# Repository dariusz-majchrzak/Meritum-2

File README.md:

# Meritum-2: Polish 8-bit Home Computer
This project was initiated with the goal of converting the old, incomplete, and often difficult-to-read documentation of the Meritum II computer into a digital CAD design. It provides a solid foundation for further research, reconstruction efforts, and experimentation by anyone interested in the technical aspects of the early days of Polish computing and the development of domestically designed 8-bit computers.<br>

All files required to build a hardware reproduction of the **Meritum 1 (Model 2) (commonly known as Meritum2)** ( https://pl.wikipedia.org/wiki/Meritum_(komputer) ) are provided in this repository. The project closely follows the design of one of the earliest microcomputers to be mass-produced in Poland.<br>

**Meritum 1 (Model 2) = Meritum2** <br>
Basic Technical Specifications:
* RAM: 48 KB (RAMD)
* ROM: 14 KB (BASIC)
* Video Memory: 1 KB (RAMS)
* Display Modes: Text — 16×64 or 16×32
* Peripherals: serial interface (i8251), parallel interface (i8255), tape interface, fdd interface (i8255)
* Colors: Monochrome
<br>
As of November 11, 2026, there is one successful build based on this PCB revision and three successful builds based on a previous PCB revision.<br>

As additional fixes were identified during testing, the repository includes an updated PCB revision (Rev. 1.2), whereas the PCB shown in the photo is Rev. 1.1. <br>
<br>

Top view of the mainboard:<br>

Side view of the computer with connectors:<br>

Example startup screen:<br>

Important notes:<br>
* Please note that this is a complex hardware project that requires solid technical expertise from anyone who decides to build it.<br>
* While significant care has been taken during the design and verification process, the project may still need additional fixes, especially if the original design included fixes implemented directly at the PCB level that were not reflected in the published schematics.

## PCBs
The clone consists of two separate PCBs:
* [Meritum2_PGW](Meritum2_PGW) (Meritum Płyta Główna) - is the main board.
* [Meritum2_KLT](Meritum2_KLT) (Meritum Klawiatura) - is a replacement keyboard that uses standard Cherry MX switches.

## ROMs
Since the licensing status of the ROMs used in the Meritum 2 computer is not clear to me, I have not included them in this repository.<br> 
Below, however, I provide links to a websites where they can be found, along with many other valuable resources:
* https://web.archive.org/web/20201023154655/https://sites.google.com/site/krzkomar/meritum-1
* https://www.planetemu.net/rom/mame-roms-merged/meritum1<br>
  
Many useful materials can also be found at: https://www.speccy.pl/news.php .

## Assembling
Although the mainboard includes several configuration jumpers, it does not require any additional settings that need to be adjusted before powering it on. The default configuration is sufficient.<br>

To connect mainboard with keyboard I have used:
-  single and double Row, 2.54mm straight, Gold PCB Female Sockets Connector
-  single and double Row, 2.54mm straight, Gold PCB Male Pin Header connector (h=29.5mm)
  
More to follow.

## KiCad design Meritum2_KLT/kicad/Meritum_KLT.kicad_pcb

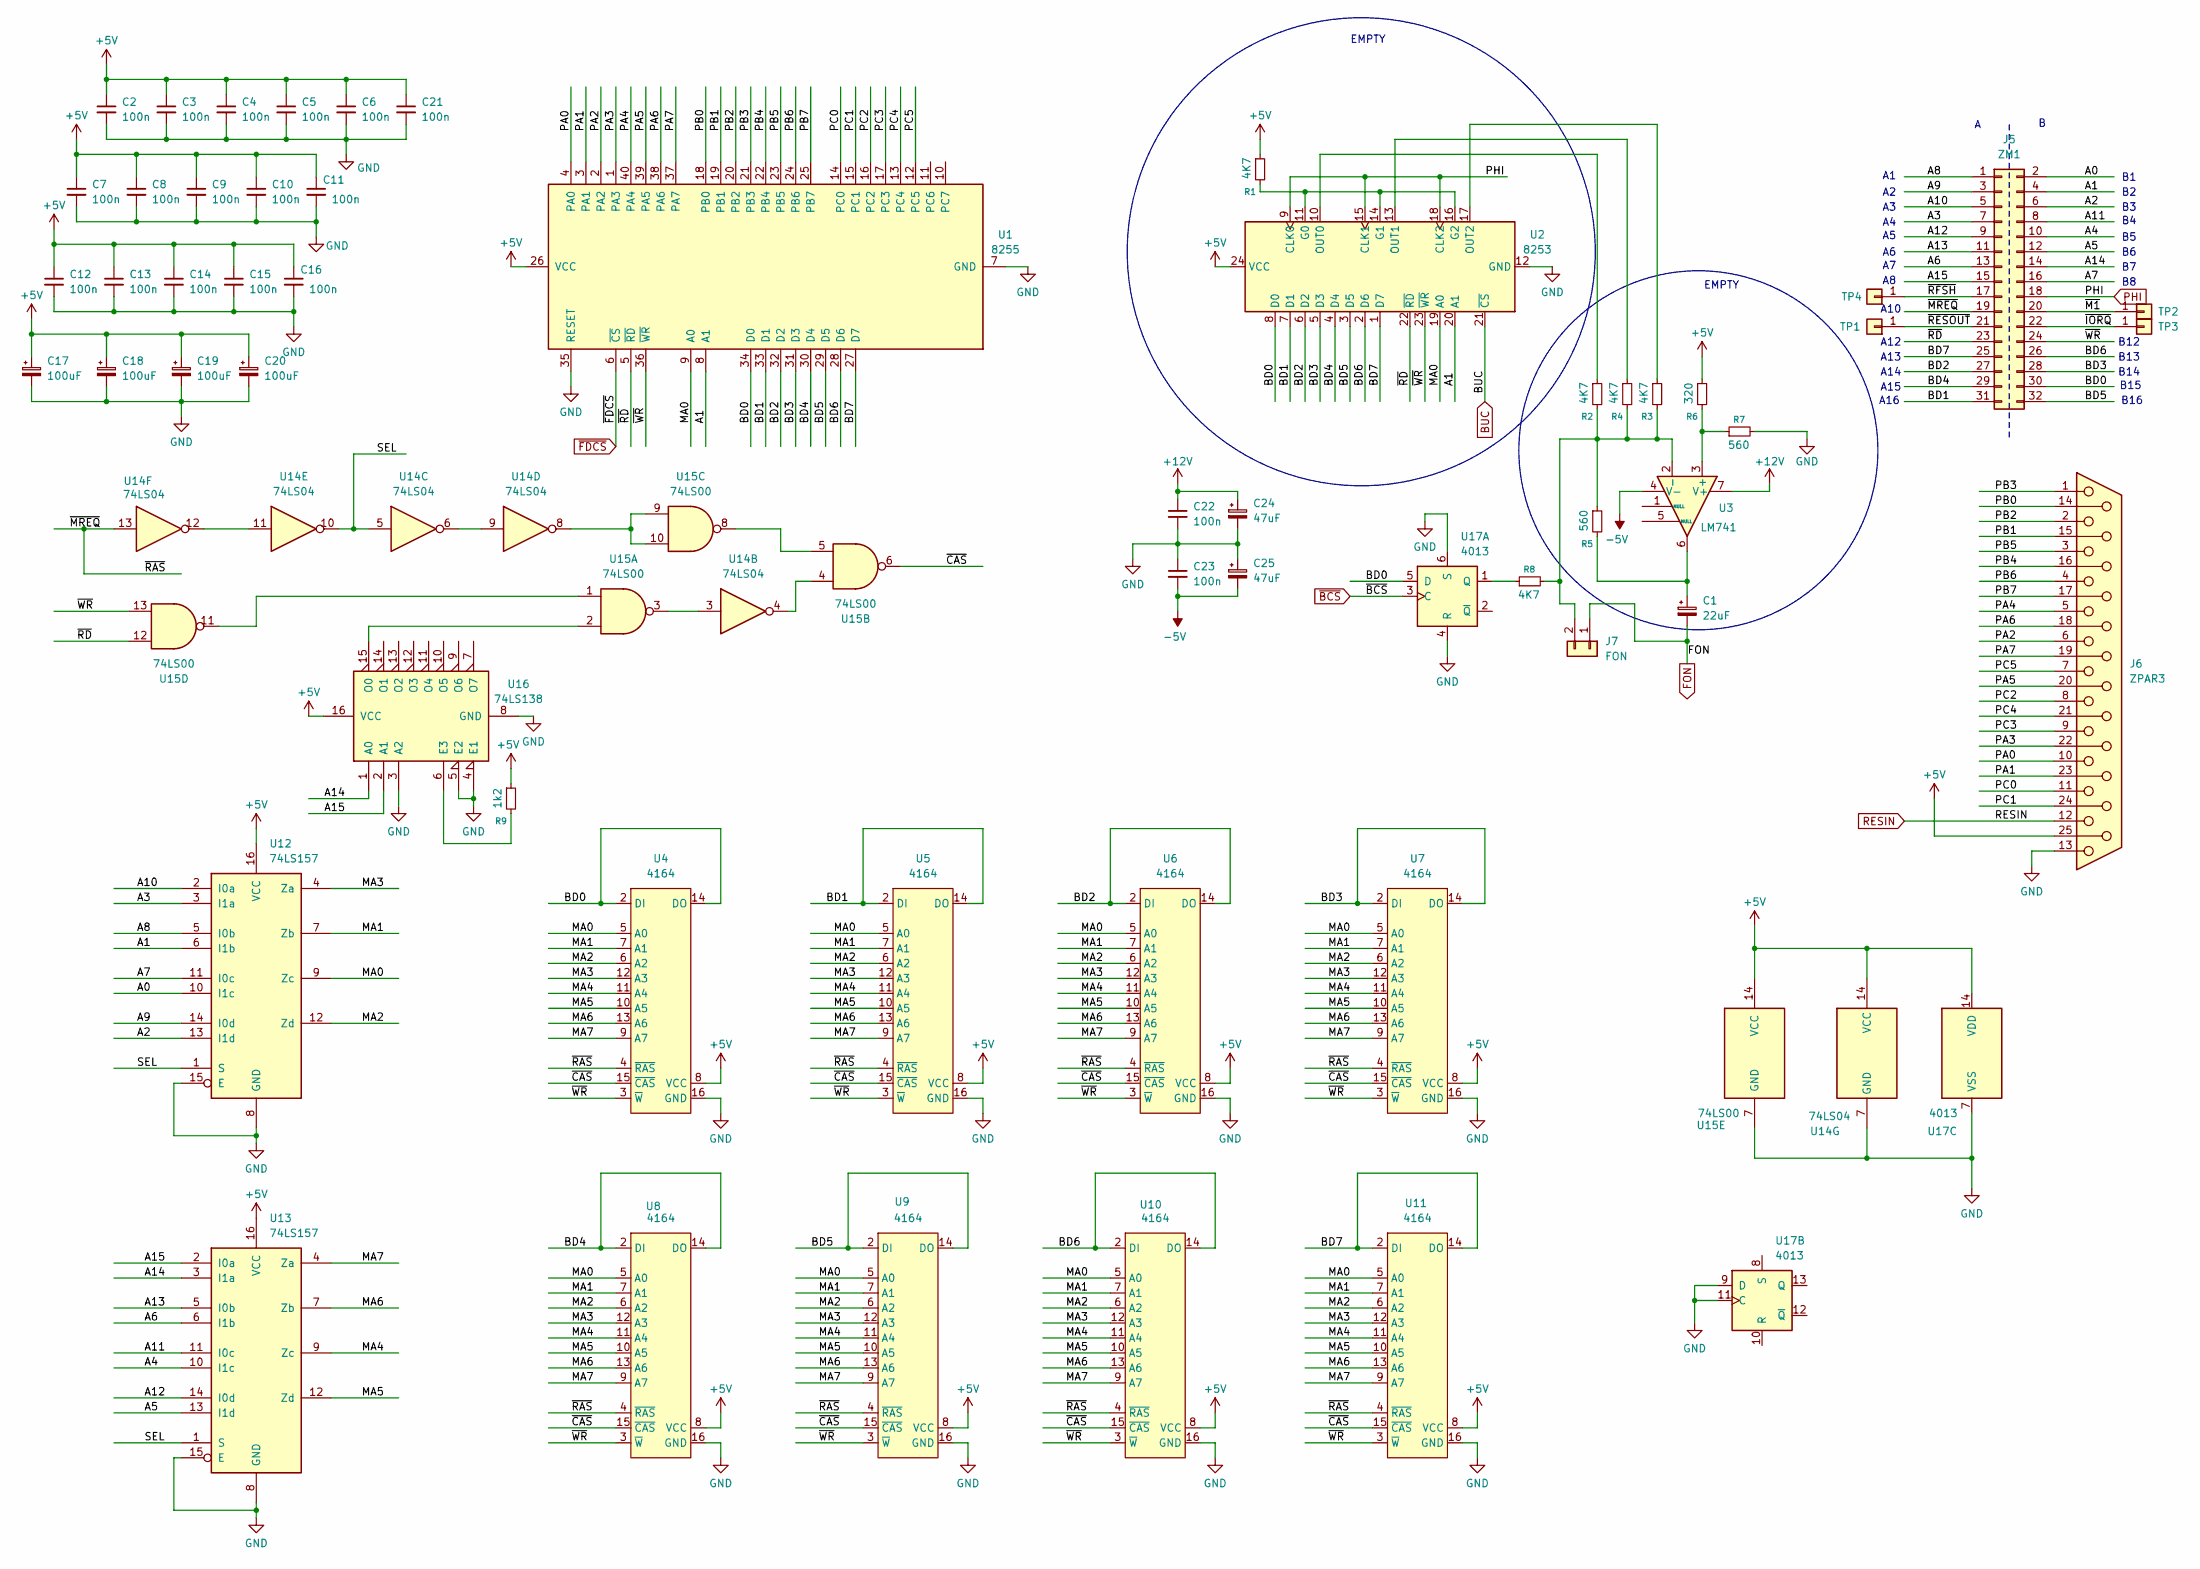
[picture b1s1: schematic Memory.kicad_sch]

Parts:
C1: 22uF; CP_Radial_D5.0mm_P2.50mm
C2, C3, C4, C5, C6, C7, C8, C9, C10, C11, C12, C13, C14, C15, C16, C21, C22, C23: 100n; C_Rect_L7.0mm_W2.5mm_P5.00mm
C17, C18, C19, C20: 100uF; CP_Radial_D5.0mm_P2.50mm
C24, C25: 47uF; CP_Radial_D5.0mm_P2.50mm
J5: ZM1; PinHeader_2x16_P2.54mm_Vertical
J6: ZPAR3; DSUB-25_Socket_Horizontal_P2.77x2.84mm_EdgePinOffset7.70mm_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
J7: FON; PinHeader_1x02_P2.54mm_Vertical
R1, R2, R3, R4, R8: 4K7; r_400
R5, R7: 560; r_400
R6: 320; r_400
R9: 1k2; r_400
TP1, TP2, TP3, TP4: TP; pin
U1: 8255; DIP-40_W15.24mm
U2: 8253; DIP-24_W15.24mm
U3: LM741; DIP-8_W7.62mm_LongPads
U4, U5, U6, U7, U8, U9, U10, U11: 4164; DIP-16_W7.62mm_LongPads
U12, U13: 74LS157; DIP-16_W7.62mm_LongPads
U14: 74LS04; DIP-14_W7.62mm_LongPads
U15: 74LS00; DIP-14_W7.62mm_LongPads
U16: 74LS138; DIP-16_W7.62mm_LongPads
U17: 4013; DIP-14_W7.62mm_LongPads

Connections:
+5V: C2.1, C3.1, C4.1, C5.1, C6.1, C7.1, C8.1, C9.1, C10.1, C11.1, C12.1, C13.1, C14.1, C15.1, C16.1, C17.1, C18.1, C19.1, C20.1, C21.1, J6.25, R1.1, R6.1, R9.1, U1.26 (VCC), U2.24 (VCC), U4.8 (VCC), U5.8 (VCC), U6.8 (VCC), U7.8 (VCC), U8.8 (VCC), U9.8 (VCC), U10.8 (VCC), U11.8 (VCC), U12.16 (VCC), U13.16 (VCC), U14.14 (VCC), U15.14 (VCC), U16.16 (VCC), U17.14 (VDD); also elsewhere on the board
+12V: C22.1, C24.1, U3.7 (V+); also elsewhere on the board
-5V: C23.2, C25.2, U3.4 (V-); also elsewhere on the board
/Memory/A0: J5.2, U12.10 (I1c)
/Memory/A1: J5.4, U1.8 (A1), U2.20 (A1), U12.6 (I1b)
/Memory/A2: J5.6, U12.13 (I1d)
/Memory/A3: J5.7, U12.3 (I1a)
/Memory/A4: J5.10, U13.10 (I1c)
/Memory/A5: J5.12, U13.13 (I1d)
/Memory/A6: J5.13, U13.6 (I1b)
/Memory/A7: J5.16, U12.11 (I0c)
/Memory/A8: J5.1, U12.5 (I0b)
/Memory/A9: J5.3, U12.14 (I0d)
/Memory/A10: J5.5, U12.2 (I0a)
/Memory/A11: J5.8, U13.11 (I0c)
/Memory/A12: J5.9, U13.14 (I0d)
/Memory/A13: J5.11, U13.5 (I0b)
/Memory/A14: J5.14, U13.3 (I1a), U16.1 (A0)
/Memory/A15: J5.15, U13.2 (I0a), U16.2 (A1)
/Memory/BD0: J5.30, U1.34 (D0), U2.8 (D0), U4.2 (DI), U4.14 (DO), U17.5 (D)
/Memory/BD1: J5.31, U1.33 (D1), U2.7 (D1), U5.2 (DI), U5.14 (DO)
/Memory/BD2: J5.27, U1.32 (D2), U2.6 (D2), U6.2 (DI), U6.14 (DO)
/Memory/BD3: J5.28, U1.31 (D3), U2.5 (D3), U7.2 (DI), U7.14 (DO)
/Memory/BD4: J5.29, U1.30 (D4), U2.4 (D4), U8.2 (DI), U8.14 (DO)
/Memory/BD5: J5.32, U1.29 (D5), U2.3 (D5), U9.2 (DI), U9.14 (DO)
/Memory/BD6: J5.26, U1.28 (D6), U2.2 (D6), U10.2 (DI), U10.14 (DO)
/Memory/BD7: J5.25, U1.27 (D7), U2.1 (D7), U11.2 (DI), U11.14 (DO)
/Memory/MA0: U1.9 (A0), U2.19 (A0), U4.5 (A0), U5.5 (A0), U6.5 (A0), U7.5 (A0), U8.5 (A0), U9.5 (A0), U10.5 (A0), U11.5 (A0), U12.9 (Zc)
/Memory/MA1: U4.7 (A1), U5.7 (A1), U6.7 (A1), U7.7 (A1), U8.7 (A1), U9.7 (A1), U10.7 (A1), U11.7 (A1), U12.7 (Zb)
/Memory/MA2: U4.6 (A2), U5.6 (A2), U6.6 (A2), U7.6 (A2), U8.6 (A2), U9.6 (A2), U10.6 (A2), U11.6 (A2), U12.12 (Zd)
/Memory/MA3: U4.12 (A3), U5.12 (A3), U6.12 (A3), U7.12 (A3), U8.12 (A3), U9.12 (A3), U10.12 (A3), U11.12 (A3), U12.4 (Za)
/Memory/MA4: U4.11 (A4), U5.11 (A4), U6.11 (A4), U7.11 (A4), U8.11 (A4), U9.11 (A4), U10.11 (A4), U11.11 (A4), U13.9 (Zc)
/Memory/MA5: U4.10 (A5), U5.10 (A5), U6.10 (A5), U7.10 (A5), U8.10 (A5), U9.10 (A5), U10.10 (A5), U11.10 (A5), U13.12 (Zd)
/Memory/MA6: U4.13 (A6), U5.13 (A6), U6.13 (A6), U7.13 (A6), U8.13 (A6), U9.13 (A6), U10.13 (A6), U11.13 (A6), U13.7 (Zb)
/Memory/MA7: U4.9 (A7), U5.9 (A7), U6.9 (A7), U7.9 (A7), U8.9 (A7), U9.9 (A7), U10.9 (A7), U11.9 (A7), U13.4 (Za)
/Memory/PA0: J6.10, U1.4 (PA0)
/Memory/PA1: J6.23, U1.3 (PA1)
/Memory/PA2: J6.6, U1.2 (PA2)
/Memory/PA3: J6.22, U1.1 (PA3)
/Memory/PA4: J6.5, U1.40 (PA4)
/Memory/PA5: J6.20, U1.39 (PA5)
/Memory/PA6: J6.18, U1.38 (PA6)
/Memory/PA7: J6.19, U1.37 (PA7)
/Memory/PB0: J6.14, U1.18 (PB0)
/Memory/PB1: J6.15, U1.19 (PB1)
/Memory/PB2: J6.2, U1.20 (PB2)
/Memory/PB3: J6.1, U1.21 (PB3)
/Memory/PB4: J6.16, U1.22 (PB4)
/Memory/PB5: J6.3, U1.23 (PB5)
/Memory/PB6: J6.4, U1.24 (PB6)
/Memory/PB7: J6.17, U1.25 (PB7)
/Memory/PC0: J6.11, U1.14 (PC0)
/Memory/PC1: J6.24, U1.15 (PC1)
/Memory/PC2: J6.8, U1.16 (PC2)
/Memory/PC3: J6.9, U1.17 (PC3)
/Memory/PC4: J6.21, U1.13 (PC4)
/Memory/PC5: J6.7, U1.12 (PC5)
/Memory/SEL: U12.1 (S), U13.1 (S), U14.5, U14.10
/Memory/~CAS: U4.15 (~CAS), U5.15 (~CAS), U6.15 (~CAS), U7.15 (~CAS), U8.15 (~CAS), U9.15 (~CAS), U10.15 (~CAS), U11.15 (~CAS), U15.6
/Memory/~IORQ: J5.22, TP3.1 (Pin_1_1)
/Memory/~M1: J5.20, TP2.1 (Pin_1_1)
/Memory/~MREQ: J5.19, U4.4 (~RAS), U5.4 (~RAS), U6.4 (~RAS), U7.4 (~RAS), U8.4 (~RAS), U9.4 (~RAS), U10.4 (~RAS), U11.4 (~RAS), U14.13
/Memory/~RD: J5.23, U1.5 (~RD), U2.22 (~RD), U15.12
/Memory/~RESOUT: J5.21, TP1.1 (Pin_1_1)
/Memory/~RFSH: J5.17, TP4.1 (Pin_1_1)
/Memory/~WR: J5.24, U1.36 (~WR), U2.23 (~WR), U4.3 (~W), U5.3 (~W), U6.3 (~W), U7.3 (~W), U8.3 (~W), U9.3 (~W), U10.3 (~W), U11.3 (~W), U15.13
BUC: U2.21 (~CS); also elsewhere on the board
FON: C1.2, J7.1; also elsewhere on the board
GND: C2.2, C3.2, C4.2, C5.2, C6.2, C7.2, C8.2, C9.2, C10.2, C11.2, C12.2, C13.2, C14.2, C15.2, C16.2, C17.2, C18.2, C19.2, C20.2, C21.2, C22.2, C23.1, C24.2, C25.1, J6.13, R7.2, U1.7 (GND), U1.35 (RESET), U2.12 (GND), U4.16 (GND), U5.16 (GND), U6.16 (GND), U7.16 (GND), U8.16 (GND), U9.16 (GND), U10.16 (GND), U11.16 (GND), U12.8 (GND), U12.15 (E), U13.8 (GND), U13.15 (E), U14.7 (GND), U15.7 (GND), U16.3 (A2), U16.4 (E1), U16.5 (E2), U16.8 (GND), U17.4 (R), U17.6 (S), U17.7 (VSS), U17.9 (D), U17.11 (C); also elsewhere on the board
unnamed: C1.1, R5.2, U3.6
unnamed: J7.2, R2.2, R3.2, R4.2, R5.1, R8.2, U3.2 (-)
unnamed: R1.2, U2.11 (G0), U2.14 (G1), U2.16 (G2)
unnamed: R2.1, U2.10 (OUT0)
unnamed: R4.1, U2.13 (OUT1)
unnamed: R3.1, U2.17 (OUT2)
unnamed: R6.2, R7.1, U3.3 (+)
unnamed: U14.3, U15.3
unnamed: U14.4, U15.4
unnamed: U14.6, U14.9
unnamed: U14.8, U15.9, U15.10
unnamed: U14.11, U14.12
unnamed: U15.1, U15.11
unnamed: U15.5, U15.8
unnamed: R9.2, U16.6 (E3)
unnamed: U15.2, U16.15 (O0)
unnamed: R8.1, U17.1 (Q)
PHI: J5.18, U2.9 (CLK0), U2.15 (CLK1), U2.18 (CLK2)
RESIN: J6.12; also elsewhere on the board
~BCS: U17.3 (C); also elsewhere on the board
~FDCS: U1.6 (~CS); also elsewhere on the board

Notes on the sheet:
B13
B12
EMPTY
A16
B15
A15
B16
A14
A13
A10
A12
B14

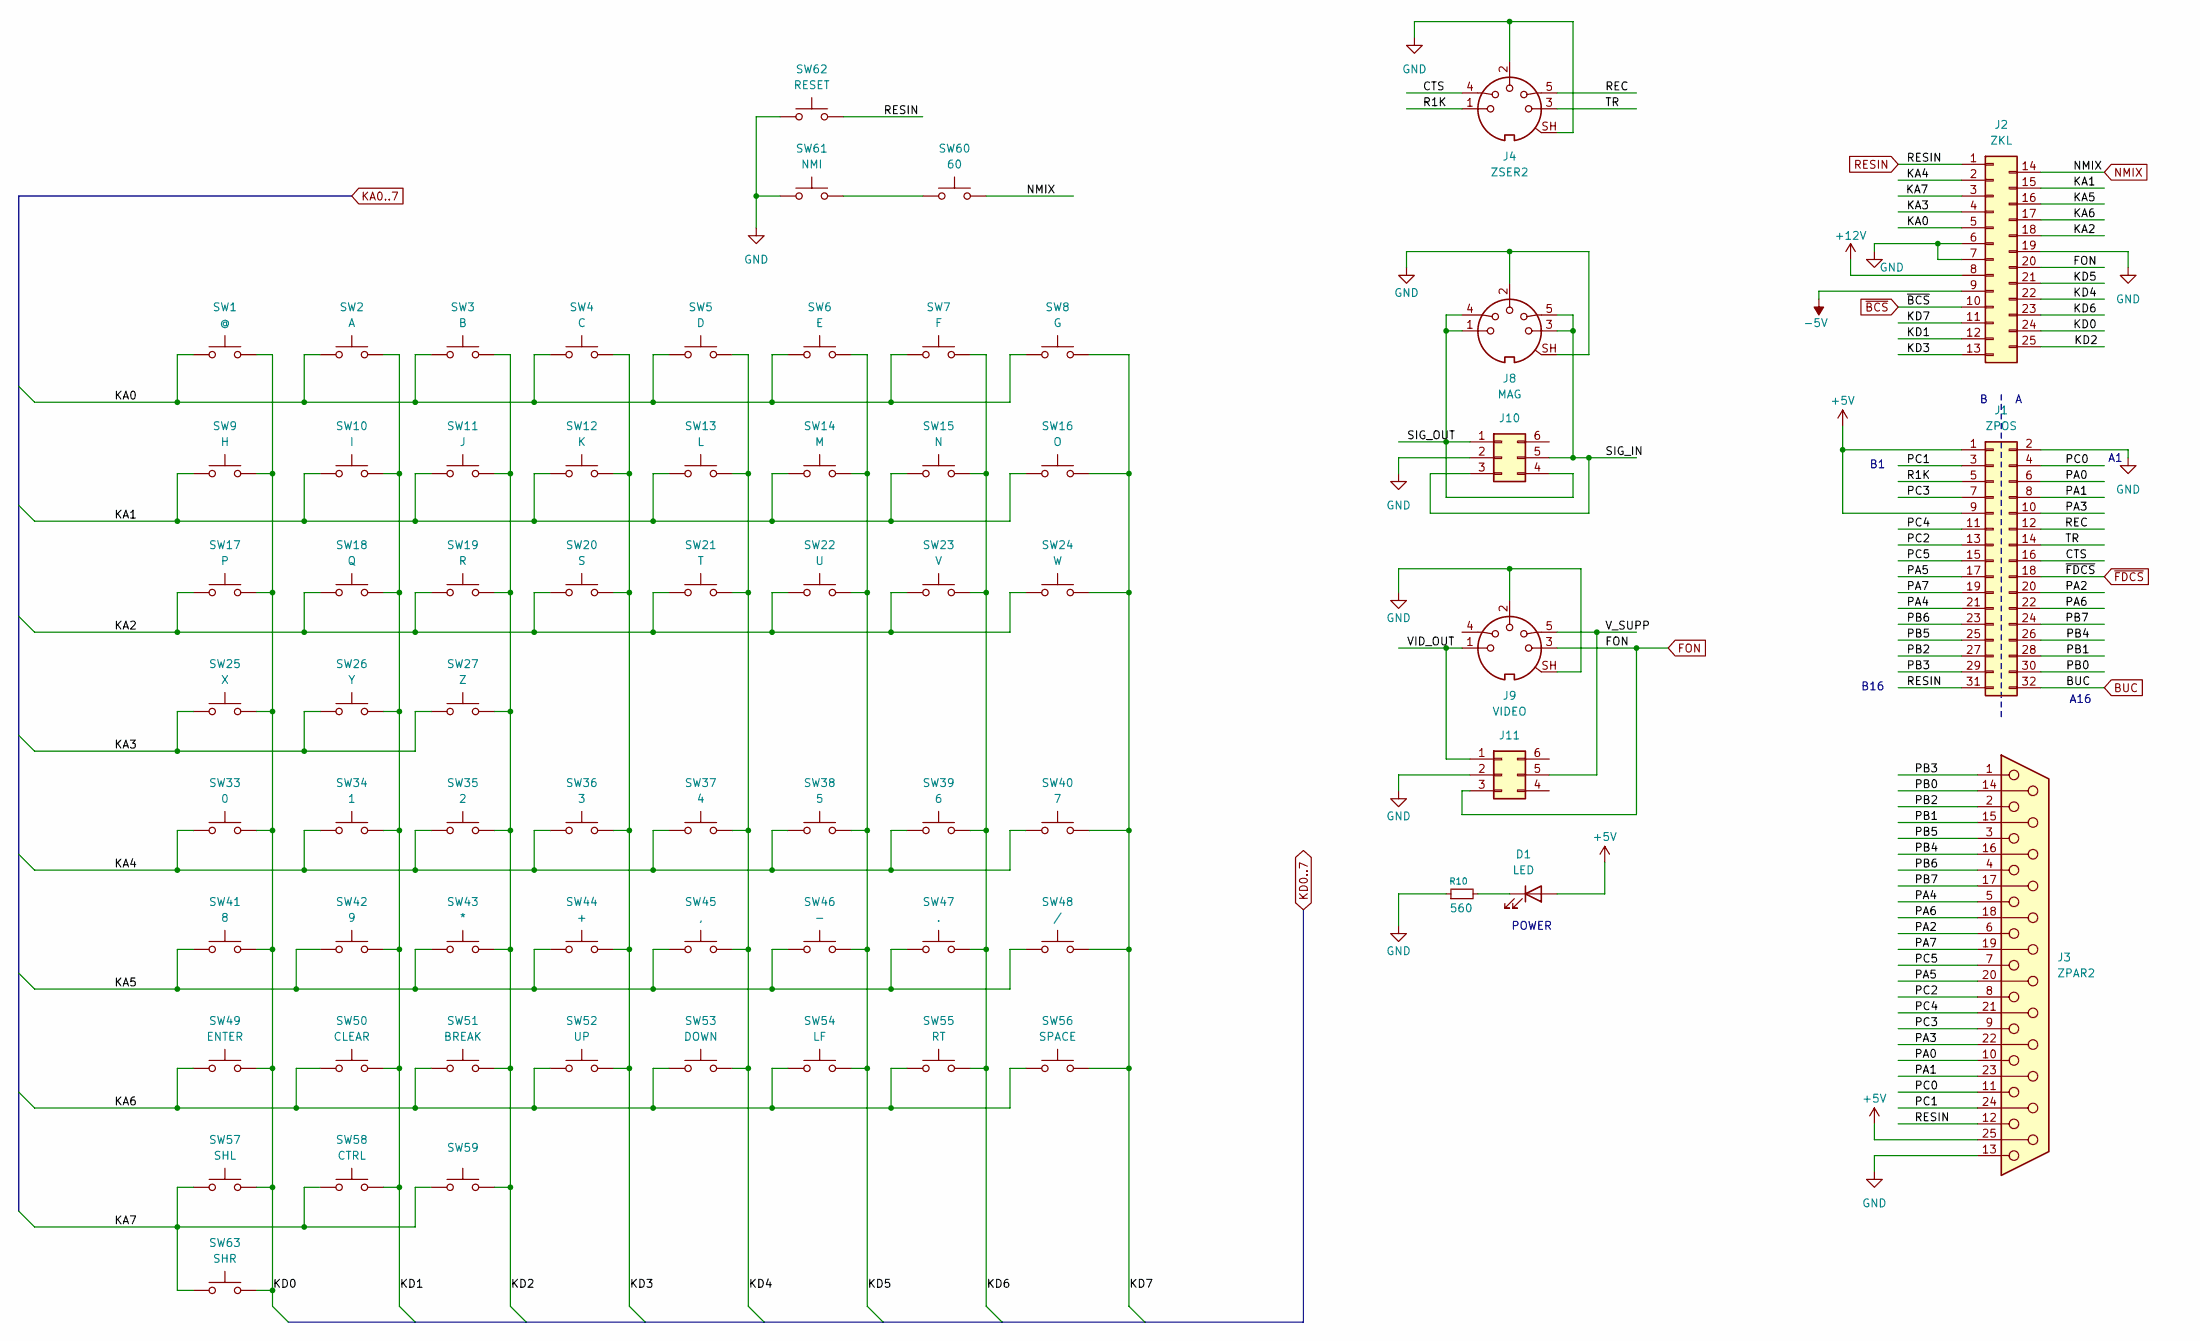
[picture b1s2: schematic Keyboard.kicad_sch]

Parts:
D1: LED; LED_D5.0mm
J1: ZPOS; PinHeader_2x16_P2.54mm_Vertical
J2: ZKL; PinSocket_25_P2.54mm_Vertical
J3: ZPAR2; DSUB-25_Socket_Horizontal_P2.77x2.84mm_EdgePinOffset7.70mm_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
J4: ZSER2; CUI_SDS-50J
J8: MAG; CUI_SDS-50J
J9: VIDEO; CUI_SDS-50J
J10, J11: Conn_02x03_Counter_Clockwise; PinHeader_2x03_P2.54mm_Vertical
R10: 560; r_400
SW1: @; SW_Cherry_MX_1.00u_PCB
SW2: A; SW_Cherry_MX_1.00u_PCB
SW3: B; SW_Cherry_MX_1.00u_PCB
SW4: C; SW_Cherry_MX_1.00u_PCB
SW5: D; SW_Cherry_MX_1.00u_PCB
SW6: E; SW_Cherry_MX_1.00u_PCB
SW7: F; SW_Cherry_MX_1.00u_PCB
SW8: G; SW_Cherry_MX_1.00u_PCB
SW9: H; SW_Cherry_MX_1.00u_PCB
SW10: I; SW_Cherry_MX_1.00u_PCB
SW11: J; SW_Cherry_MX_1.00u_PCB
SW12: K; SW_Cherry_MX_1.00u_PCB
SW13: L; SW_Cherry_MX_1.00u_PCB
SW14: M; SW_Cherry_MX_1.00u_PCB
SW15: N; SW_Cherry_MX_1.00u_PCB
SW16: O; SW_Cherry_MX_1.00u_PCB
SW17: P; SW_Cherry_MX_1.00u_PCB
SW18: Q; SW_Cherry_MX_1.00u_PCB
SW19: R; SW_Cherry_MX_1.00u_PCB
SW20: S; SW_Cherry_MX_1.00u_PCB
SW21: T; SW_Cherry_MX_1.00u_PCB
SW22: U; SW_Cherry_MX_1.00u_PCB
SW23: V; SW_Cherry_MX_1.00u_PCB
SW24: W; SW_Cherry_MX_1.00u_PCB
SW25: X; SW_Cherry_MX_1.00u_PCB
SW26: Y; SW_Cherry_MX_1.00u_PCB
SW27: Z; SW_Cherry_MX_1.00u_PCB
SW33: 0; SW_Cherry_MX_1.00u_PCB
SW34: 1; SW_Cherry_MX_1.00u_PCB
SW35: 2; SW_Cherry_MX_1.00u_PCB
SW36: 3; SW_Cherry_MX_1.00u_PCB
SW37: 4; SW_Cherry_MX_1.00u_PCB
SW38: 5; SW_Cherry_MX_1.00u_PCB
SW39: 6; SW_Cherry_MX_1.00u_PCB
SW40: 7; SW_Cherry_MX_1.00u_PCB
SW41: 8; SW_Cherry_MX_1.00u_PCB
SW42: 9; SW_Cherry_MX_1.00u_PCB
SW43: *; SW_Cherry_MX_1.00u_PCB
SW44: +; SW_Cherry_MX_1.00u_PCB
SW45: ,; SW_Cherry_MX_1.00u_PCB
SW46: -; SW_Cherry_MX_1.00u_PCB
SW47: .; SW_Cherry_MX_1.00u_PCB
SW48: /; SW_Cherry_MX_1.00u_PCB
SW49: ENTER; SW_Cherry_MX_1.50u_PCB
SW50: CLEAR; SW_Cherry_MX_1.00u_PCB
SW51: BREAK; SW_Cherry_MX_1.00u_PCB
SW52: UP; SW_Cherry_MX_1.00u_PCB
SW53: DOWN; SW_Cherry_MX_1.00u_PCB
SW54: LF; SW_Cherry_MX_1.00u_PCB
SW55: RT; SW_Cherry_MX_1.00u_PCB
SW56: SPACE; SW_Cherry_MX_6.25u_PCB
SW57: SHL; SW_Cherry_MX_1.00u_PCB
SW58: CTRL; SW_Cherry_MX_1.50u_PCB
SW59: SW_Cherry_MX_1.00u_PCB
SW60: 60; SW_Cherry_MX_1.50u_PCB
SW61: NMI; SW_Cherry_MX_1.00u_PCB
SW62: RESET; SW_Push_2P2T_Toggle_CK_PVA2OAH5xxxxxxV2
SW63: SHR; SW_Cherry_MX_1.00u_PCB

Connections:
+5V: D1.2 (A), J1.1, J1.9, J3.25; also elsewhere on the board
+12V: J2.8; also elsewhere on the board
-5V: J2.9; also elsewhere on the board
/Keyboard/CTS: J1.16, J4.4
/Keyboard/KA0: J2.5, SW1.1, SW2.1, SW3.1, SW4.1, SW5.1, SW6.1, SW7.1, SW8.1
/Keyboard/KA1: J2.15, SW9.1, SW10.1, SW11.1, SW12.1, SW13.1, SW14.1, SW15.1, SW16.1
/Keyboard/KA2: J2.18, SW17.1, SW18.1, SW19.1, SW20.1, SW21.1, SW22.1, SW23.1, SW24.1
/Keyboard/KA3: J2.4, SW25.1, SW26.1, SW27.1
/Keyboard/KA4: J2.2, SW33.1, SW34.1, SW35.1, SW36.1, SW37.1, SW38.1, SW39.1, SW40.1
/Keyboard/KA5: J2.16, SW41.1, SW42.1, SW43.1, SW44.1, SW45.1, SW46.1, SW47.1, SW48.1
/Keyboard/KA6: J2.17, SW49.1, SW50.1, SW51.1, SW52.1, SW53.1, SW54.1, SW55.1, SW56.1
/Keyboard/KA7: J2.3, SW57.1, SW58.1, SW59.1, SW63.1
/Keyboard/KD0: J2.24, SW1.2, SW9.2, SW17.2, SW25.2, SW33.2, SW41.2, SW49.2, SW57.2, SW63.2
/Keyboard/KD1: J2.12, SW2.2, SW10.2, SW18.2, SW26.2, SW34.2, SW42.2, SW50.2, SW58.2
/Keyboard/KD2: J2.25, SW3.2, SW11.2, SW19.2, SW27.2, SW35.2, SW43.2, SW51.2, SW59.2
/Keyboard/KD3: J2.13, SW4.2, SW12.2, SW20.2, SW36.2, SW44.2, SW52.2
/Keyboard/KD4: J2.22, SW5.2, SW13.2, SW21.2, SW37.2, SW45.2, SW53.2
/Keyboard/KD5: J2.21, SW6.2, SW14.2, SW22.2, SW38.2, SW46.2, SW54.2
/Keyboard/KD6: J2.23, SW7.2, SW15.2, SW23.2, SW39.2, SW47.2, SW55.2
/Keyboard/KD7: J2.11, SW8.2, SW16.2, SW24.2, SW40.2, SW48.2, SW56.2
/Keyboard/PA0: J1.6, J3.10
/Keyboard/PA1: J1.8, J3.23
/Keyboard/PA2: J1.20, J3.6
/Keyboard/PA3: J1.10, J3.22
/Keyboard/PA4: J1.21, J3.5
/Keyboard/PA5: J1.17, J3.20
/Keyboard/PA6: J1.22, J3.18
/Keyboard/PA7: J1.19, J3.19
/Keyboard/PB0: J1.30, J3.14
/Keyboard/PB1: J1.28, J3.15
/Keyboard/PB2: J1.27, J3.2
/Keyboard/PB3: J1.29, J3.1
/Keyboard/PB4: J1.26, J3.16
/Keyboard/PB5: J1.25, J3.3
/Keyboard/PB6: J1.23, J3.4
/Keyboard/PB7: J1.24, J3.17
/Keyboard/PC0: J1.4, J3.11
/Keyboard/PC1: J1.3, J3.24
/Keyboard/PC2: J1.13, J3.8
/Keyboard/PC3: J1.7, J3.9
/Keyboard/PC4: J1.11, J3.21
/Keyboard/PC5: J1.15, J3.7
/Keyboard/R1K: J1.5, J4.1
/Keyboard/REC: J1.12, J4.5
/Keyboard/SIG_IN: J8.3, J8.5, J10.3, J10.5
/Keyboard/SIG_OUT: J8.1, J8.4, J10.1, J10.4
/Keyboard/TR: J1.14, J4.3
/Keyboard/VID_OUT: J9.1, J11.1
/Keyboard/V_SUPP: J9.5, J11.5
BUC: J1.32; also elsewhere on the board
FON: J2.20, J9.3, J11.3; also elsewhere on the board
GND: J1.2, J2.6, J2.7, J2.19, J3.13, J4.2, J4.SH, J8.2, J8.SH, J9.2, J9.SH, J10.2, J11.2, R10.1, SW61.1, SW62.1; also elsewhere on the board
NMIX: J2.14, SW60.2
unnamed: D1.1 (K), R10.2
unnamed: SW60.1, SW61.2
RESIN: J1.31, J2.1, J3.12, SW62.2; also elsewhere on the board
~BCS: J2.10; also elsewhere on the board
~FDCS: J1.18; also elsewhere on the board

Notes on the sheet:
POWER
B16
A16

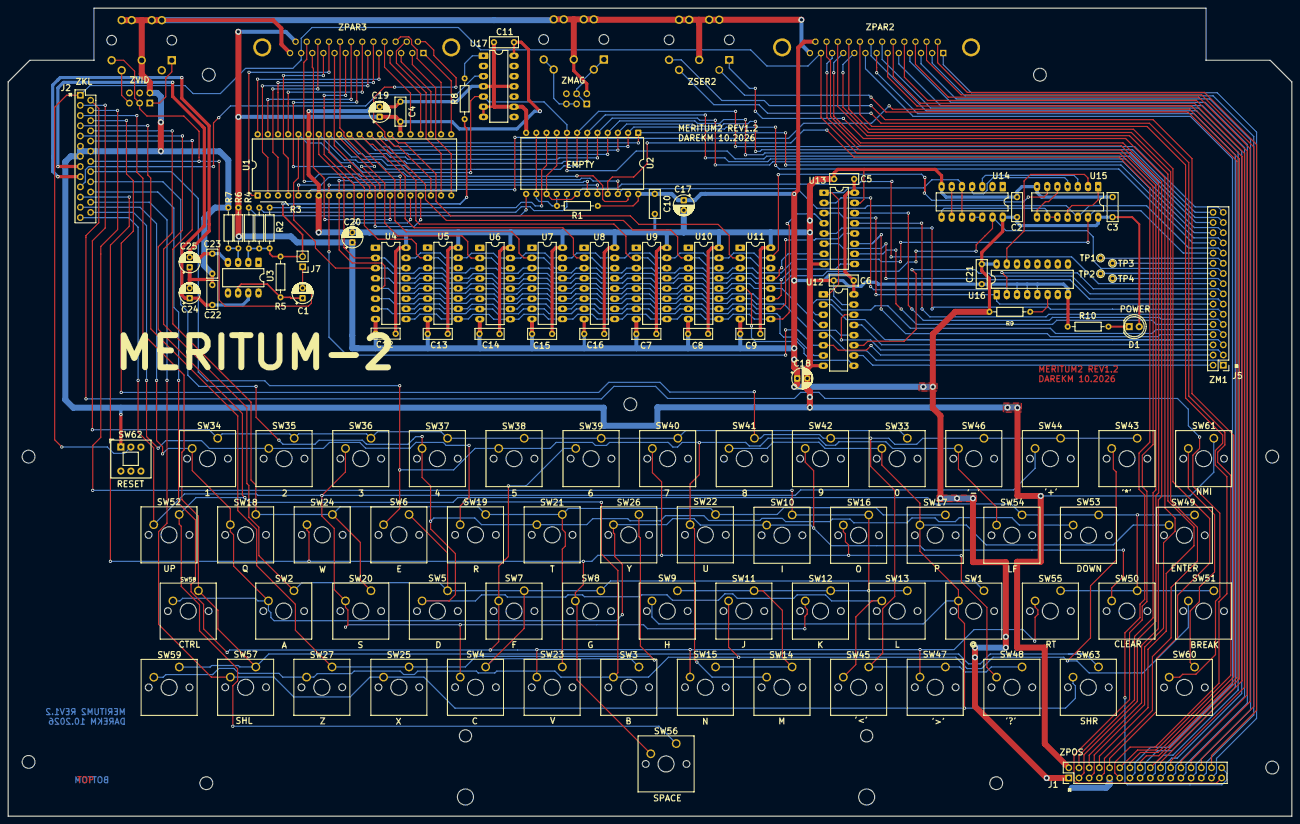
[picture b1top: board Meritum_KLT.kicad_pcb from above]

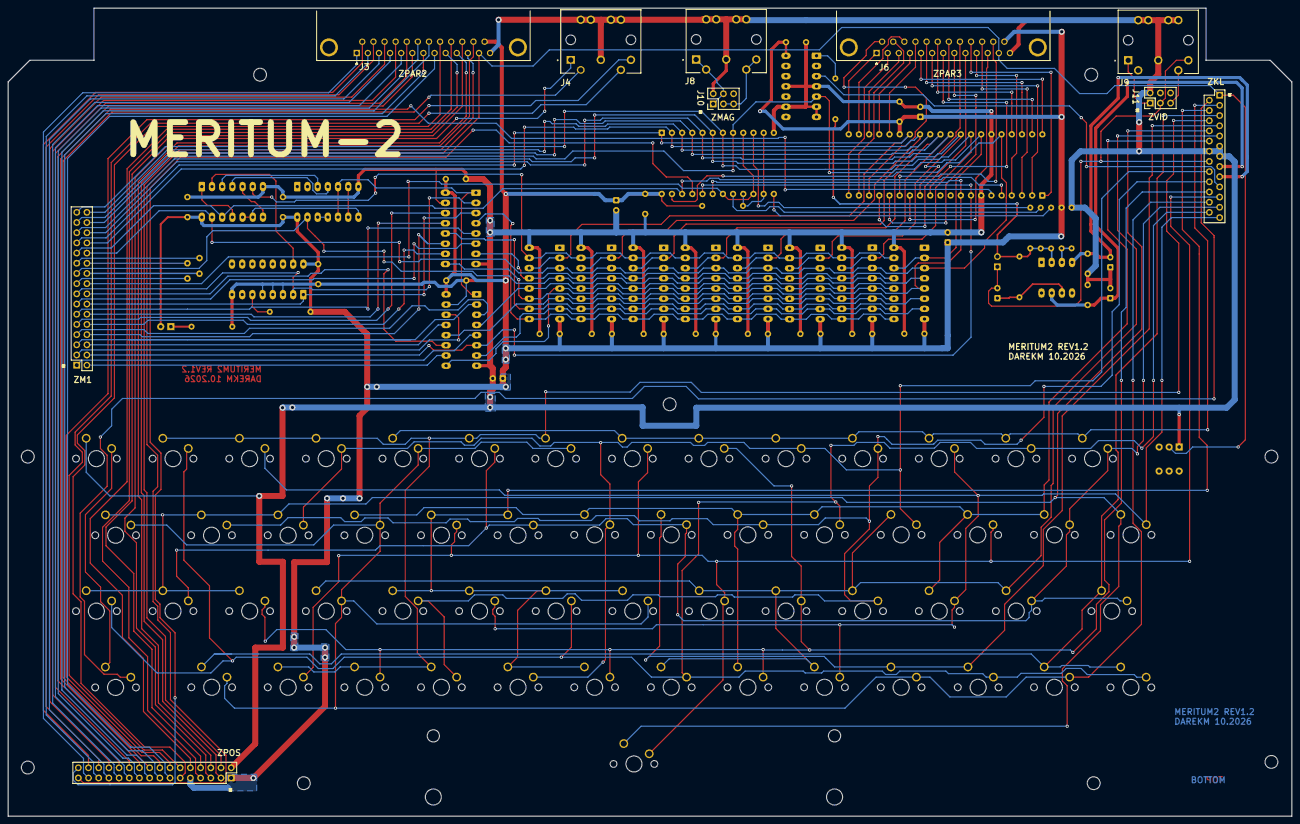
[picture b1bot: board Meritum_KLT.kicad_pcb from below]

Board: 2 copper layers, 320.0 x 201.4 mm, 126 parts (7 on the bottom side), 139 nets.
